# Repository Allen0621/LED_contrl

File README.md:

# LED_contrl
利用arduino控制燈條做出可控的櫥櫃燈

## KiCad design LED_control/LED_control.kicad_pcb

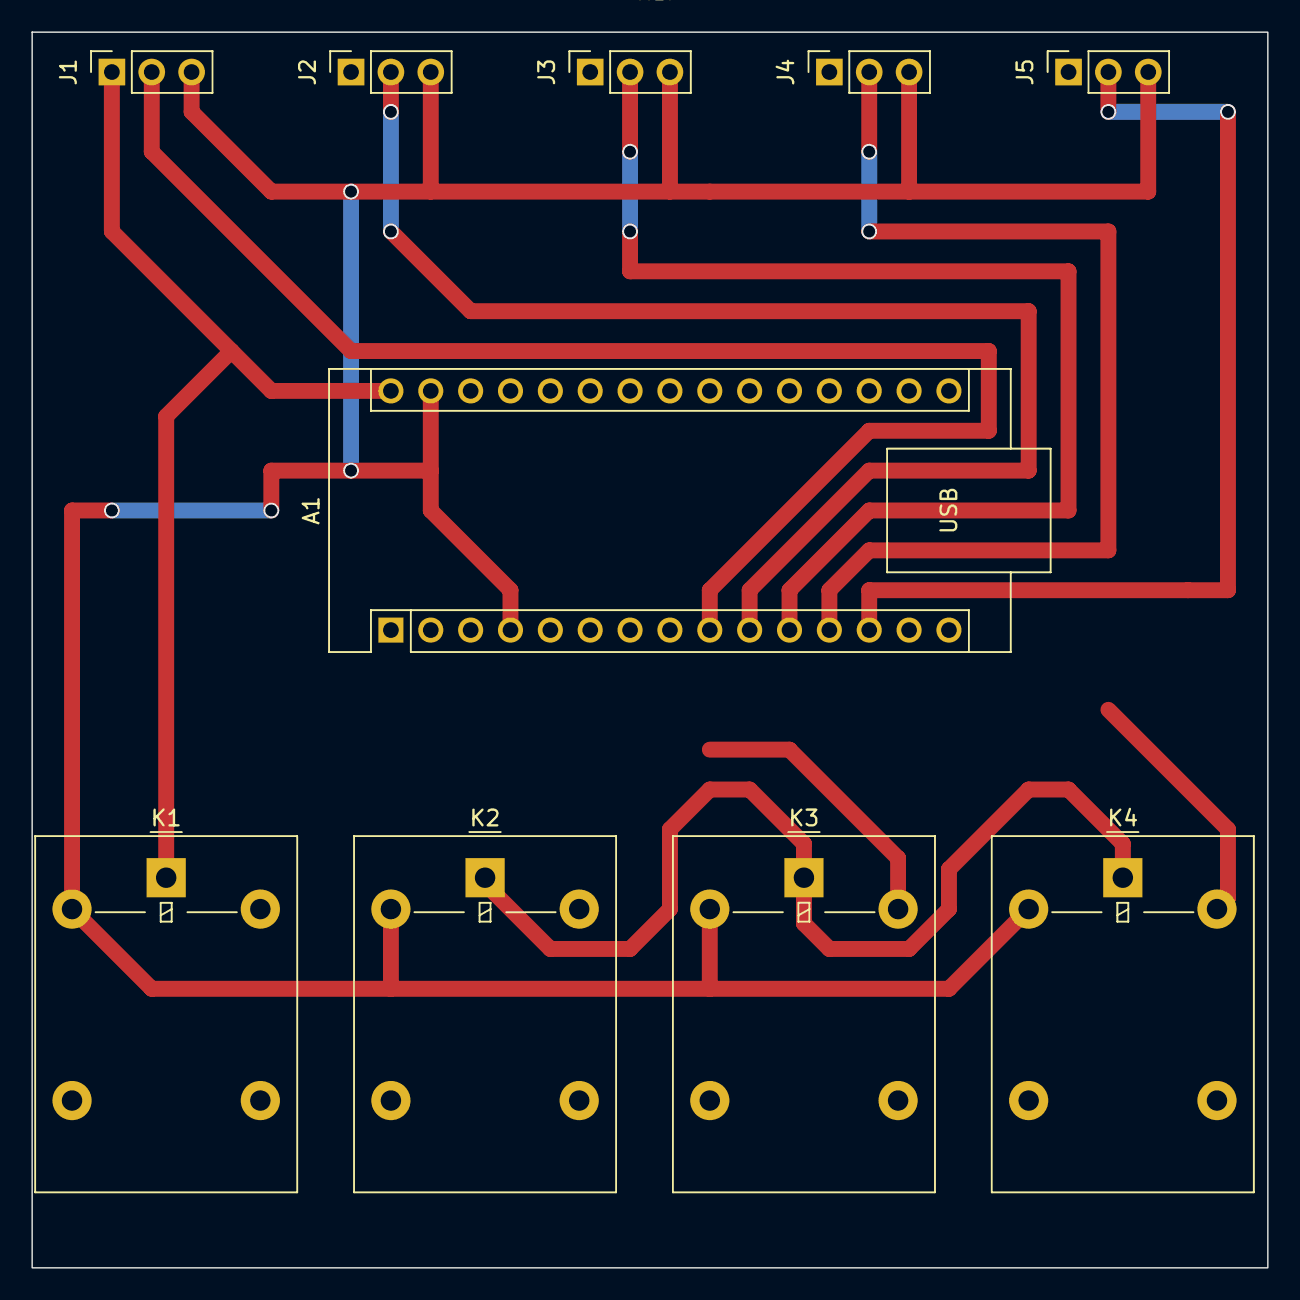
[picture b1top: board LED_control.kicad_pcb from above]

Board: 2 copper layers, 78.7 x 78.7 mm, 10 parts (0 on the bottom side), 11 nets.

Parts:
A1: Arduino_Nano_Every; Arduino_Nano
J1, J2, J3, J4, J5: Conn_01x03_Socket; PinSocket_1x03_P2.54mm_Vertical
K1, K2, K3, K4: G5LE-1; Relay_SPDT_Omron-G5LE-1

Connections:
+5V: A1.30 (VIN), J1.1 (VCC), J2.1 (VCC), J3.1 (VCC), J4.1 (VCC), J5.1 (VCC), K1.1, K2.1, K3.1, K4.1
/D2: A1.5 (D2), K1.5
/D3: A1.6 (D3), K2.5
/D4: A1.7 (D4), K3.5
/D5: A1.8 (D5), K4.5
/D6: A1.9 (D6), J1.2
/D7: A1.10 (D7), J2.2
/D8: A1.11 (D8), J3.2
/D9: A1.12 (D9), J4.2
/D10: A1.13 (D10), J5.2
Earth: A1.4 (GND), A1.29 (GND), J1.3, J2.3, J3.3, J4.3, J5.3, K1.2, K2.2, K3.2, K4.2

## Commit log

2026-04-18 實體運行影片
